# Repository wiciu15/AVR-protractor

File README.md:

# AVR-protractor
ATMega8 based protractor with SSD1306 OLED and LIS3DH accelerometer.

Schematic and PCB made in KiCAD. Firmware project created in Atmel Studio 7. Makefile available.

Known issue - ISP header is flipped, don't try to connect it to AVRISP with kanda ribbon cable, it's gonna make a short.

Firmware is working, but some extra features are still WIP (@TODO in main.c)

Display driver made by @tibounise (https://github.com/tibounise/SSD1306-AVR) slightly modified by me to save RAM for framebuffer.

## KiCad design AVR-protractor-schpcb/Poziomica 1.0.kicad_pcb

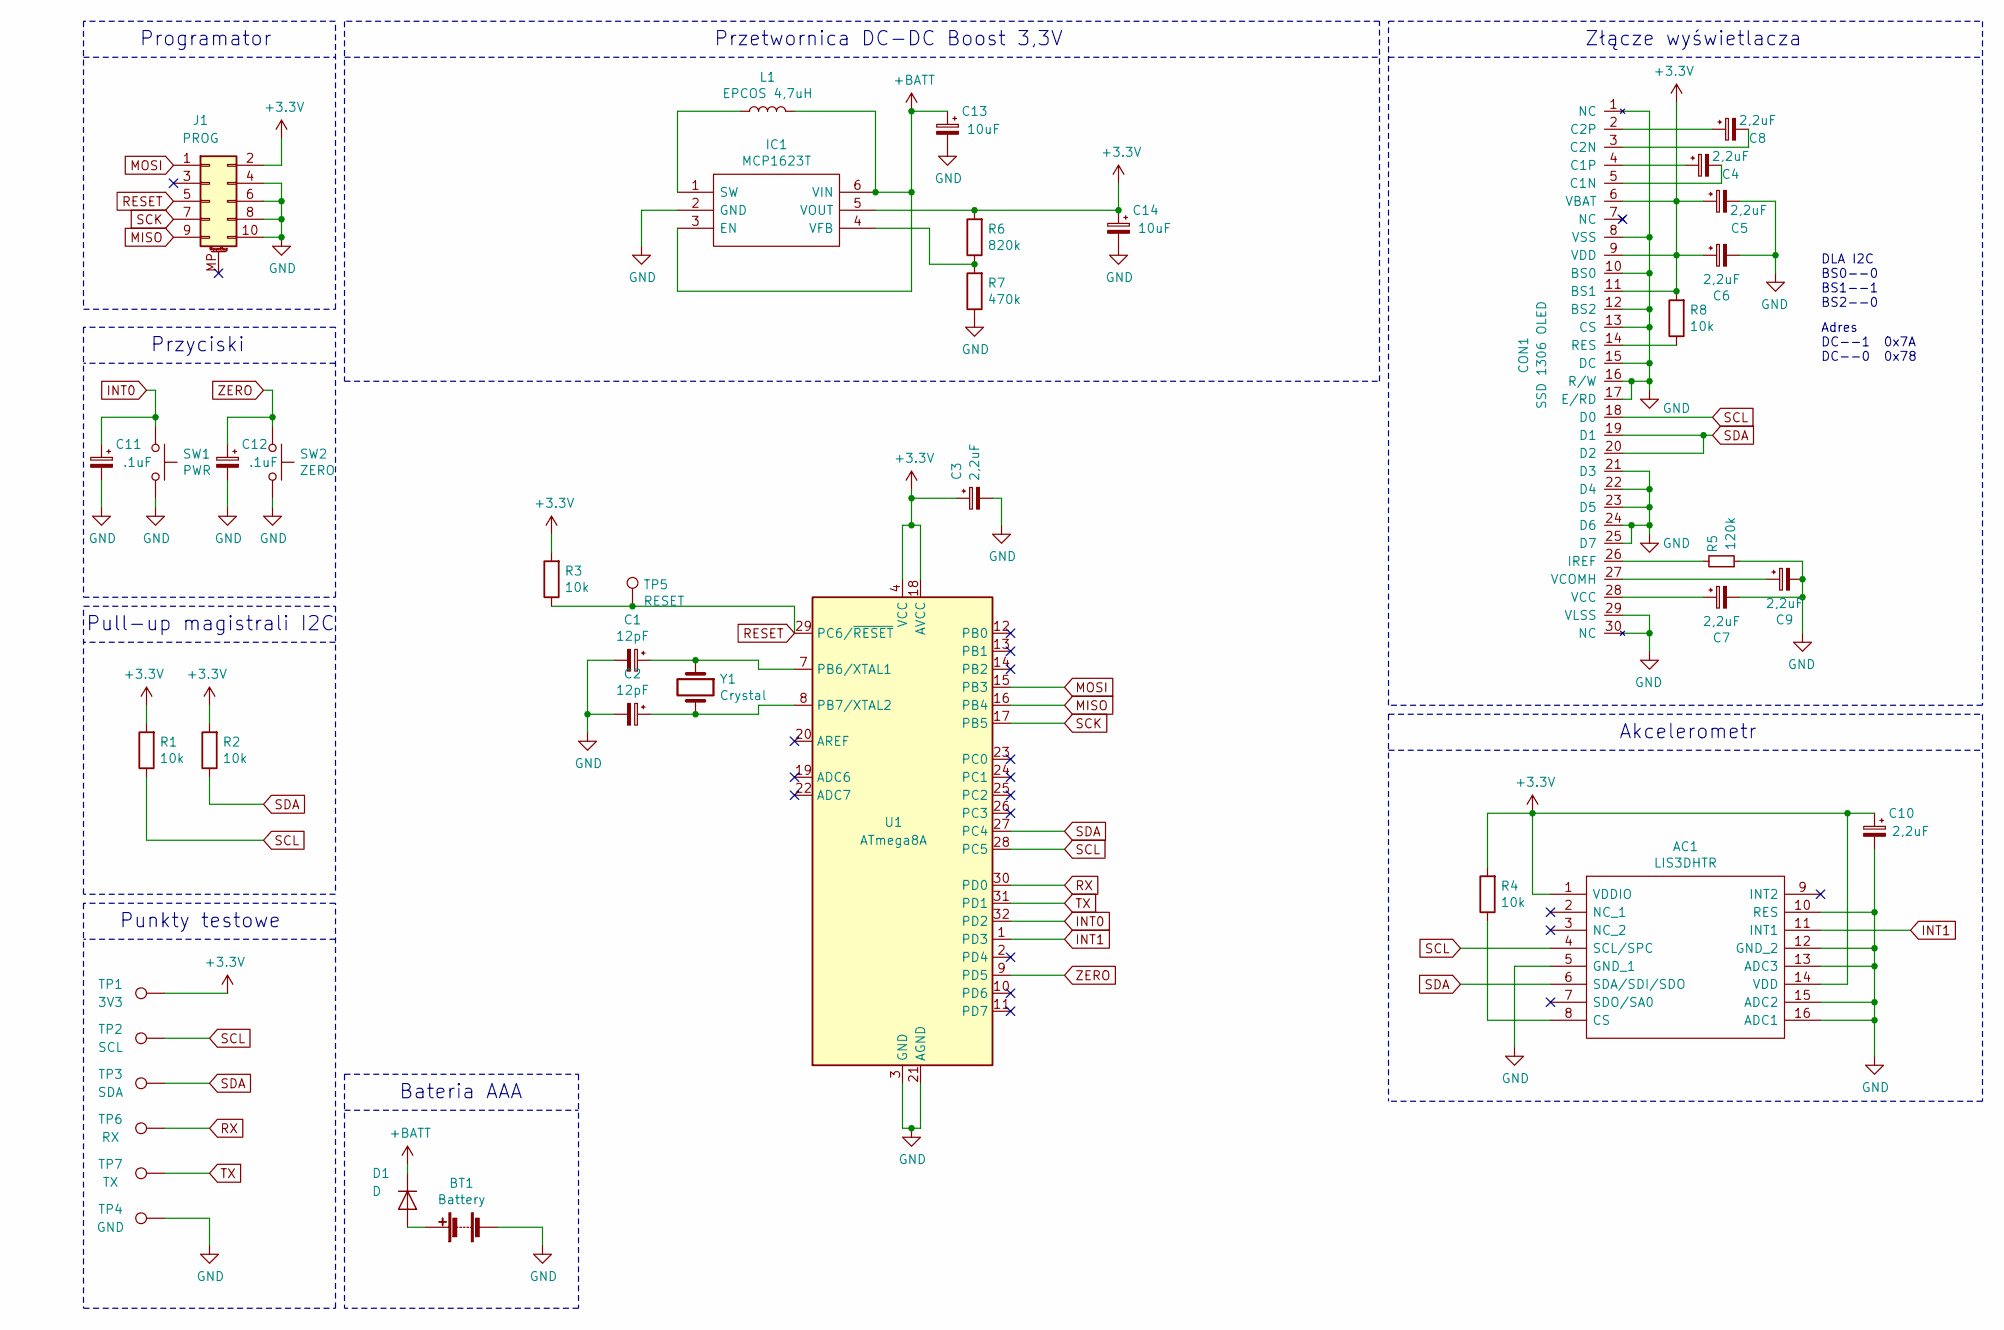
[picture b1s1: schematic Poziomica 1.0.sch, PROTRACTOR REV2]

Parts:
AC1: LIS3DHTR; LIS3DH_BigPad; Mouser Part Number 511-LIS3DHTR
BT1: Battery; 1021BatteryAAA
C1, C2: 12pF; C_0805_2012Metric_Pad1.15x1.40mm_HandSolder
C3, C4, C5, C6, C7, C8, C9, C10: 2,2uF; C_0805_2012Metric_Pad1.15x1.40mm_HandSolder
C11, C12: .1uF; C_0603_1608Metric_Pad1.05x0.95mm_HandSolder
C13, C14: 10uF; C_0805_2012Metric_Pad1.15x1.40mm_HandSolder
CON1: SSD 1306 OLED; SSD1306
D1: D; D_SOT-23_ANK
IC1: MCP1623T; SOT95P270X145-6N; Mouser Part Number 579-MCP1623T-I/CHY
J1: PROG
L1: EPCOS 4,7uH; IND-B82462G4
R1, R2, R3, R4, R8: 10k; R_0805_2012Metric_Pad1.15x1.40mm_HandSolder
R5: 120k; R_1206_3216Metric_Pad1.42x1.75mm_HandSolder
R6: 820k; R_0805_2012Metric_Pad1.15x1.40mm_HandSolder
R7: 470k; R_0805_2012Metric_Pad1.15x1.40mm_HandSolder
SW1: PWR; 7914J1000E
SW2: ZERO; 7914J1000E
TP1: 3V3; TestPoint_Pad_D2.0mm
TP2: SCL; TestPoint_Pad_D2.0mm
TP3: SDA; TestPoint_Pad_D2.0mm
TP4: GND; TestPoint_Pad_D2.0mm
TP5: RESET; TestPoint_Pad_D2.0mm
TP6: RX; TestPoint_Pad_D2.0mm
TP7: TX; TestPoint_Pad_D2.0mm
U1: ATmega8A; TQFP-32_7x7mm_P0.8mm
Y1: Crystal; Crystal_HC49-U_Vertical

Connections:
+3V3: AC1.1 (VDDIO), AC1.14 (VDD), C3.1, C5.1, C6.1, C10.1, C14.1, CON1.6 (VBAT), CON1.9 (VDD), CON1.11 (BS1), IC1.5 (VOUT), J1.2, R1.2, R2.2, R3.2, R4.2, R6.2, R8.2, TP1.1, U1.4 (VCC), U1.6 (VCC), U1.18 (AVCC)
+BATT: C13.1, D1.1 (K), IC1.3 (EN), IC1.6 (VIN), L1.2
GND: AC1.5 (GND_1), AC1.10 (RES), AC1.12 (GND_2), AC1.13 (ADC3), AC1.15 (ADC2), AC1.16 (ADC1), BT1.2 (-), C1.2, C2.2, C3.2, C5.2, C6.2, C7.2, C9.2, C10.2, C11.2, C12.2, C13.2, C14.2, CON1.1 (NC), CON1.8 (VSS), CON1.10 (BS0), CON1.12 (BS2), CON1.13 (CS), CON1.15 (DC), CON1.16 (R/W), CON1.17 (E/RD), CON1.21 (D3), CON1.22 (D4), CON1.23 (D5), CON1.24 (D6), CON1.25 (D7), CON1.29 (VLSS), CON1.30 (NC), IC1.2 (GND), J1.4, J1.6, J1.8, J1.10, R5.1, R7.1, SW1.2, SW2.2, TP4.1, U1.3 (GND), U1.5 (GND), U1.21 (AGND)
INT0: C11.1, SW1.1, U1.32 (PD2)
INT1: AC1.11 (INT1), U1.1 (PD3)
MISO: J1.9, U1.16 (PB4)
MOSI: J1.1, U1.15 (PB3)
unnamed: AC1.8 (CS), R4.1
unnamed: BT1.1 (+), D1.2 (A)
unnamed: C1.1, U1.7 (PB6/XTAL1), Y1.1
unnamed: C2.1, U1.8 (PB7/XTAL2), Y1.2
unnamed: C4.1, CON1.4 (C1P)
unnamed: C4.2, CON1.5 (C1N)
unnamed: C7.1, CON1.28 (VCC)
unnamed: C8.1, CON1.2 (C2P)
unnamed: C8.2, CON1.3 (C2N)
unnamed: C9.1, CON1.27 (VCOMH)
unnamed: CON1.14 (RES), R8.1
unnamed: CON1.26 (IREF), R5.2
unnamed: IC1.1 (SW), L1.1
unnamed: IC1.4 (VFB), R6.1, R7.2
RESET: J1.5, R3.1, TP5.1, U1.29 (PC6/~RESET)
RX: TP6.1, U1.30 (PD0)
SCK: J1.7, U1.17 (PB5)
SCL: AC1.4 (SCL/SPC), CON1.18 (D0), R1.1, TP2.1, U1.28 (PC5)
SDA: AC1.6 (SDA/SDI/SDO), CON1.19 (D1), CON1.20 (D2), R2.1, TP3.1, U1.27 (PC4)
TX: TP7.1, U1.31 (PD1)
ZERO: C12.1, SW2.1, U1.9 (PD5)

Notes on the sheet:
DLA I2C BS0--0 BS1--1 BS2--0
Złącze wyświetlacza
Akcelerometr
Punkty testowe
Pull-up magistrali I2C
Przyciski
Programator
Bateria AAA
Przetwornica DC-DC Boost 3,3V
Adres DC--1 0x7A DC--0 0x78

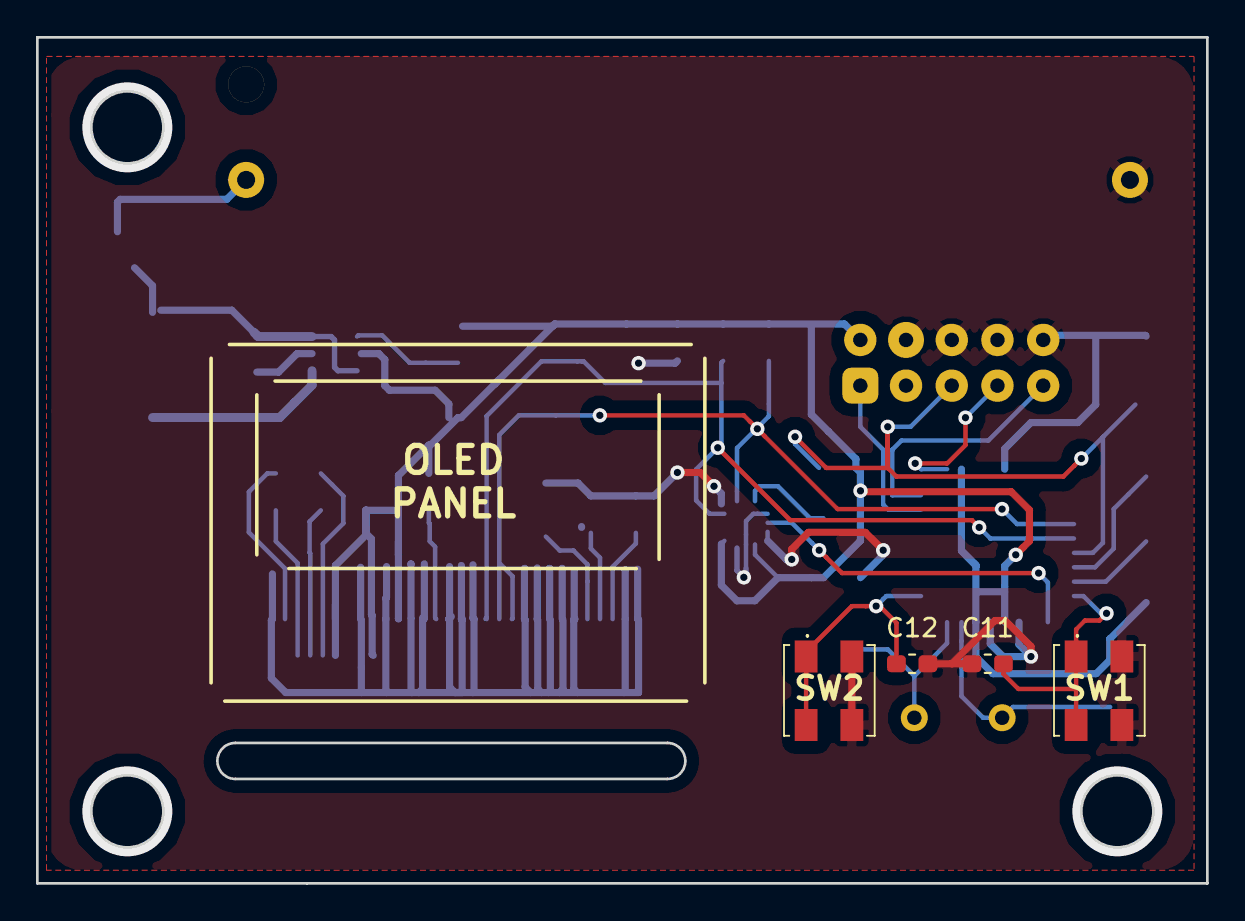
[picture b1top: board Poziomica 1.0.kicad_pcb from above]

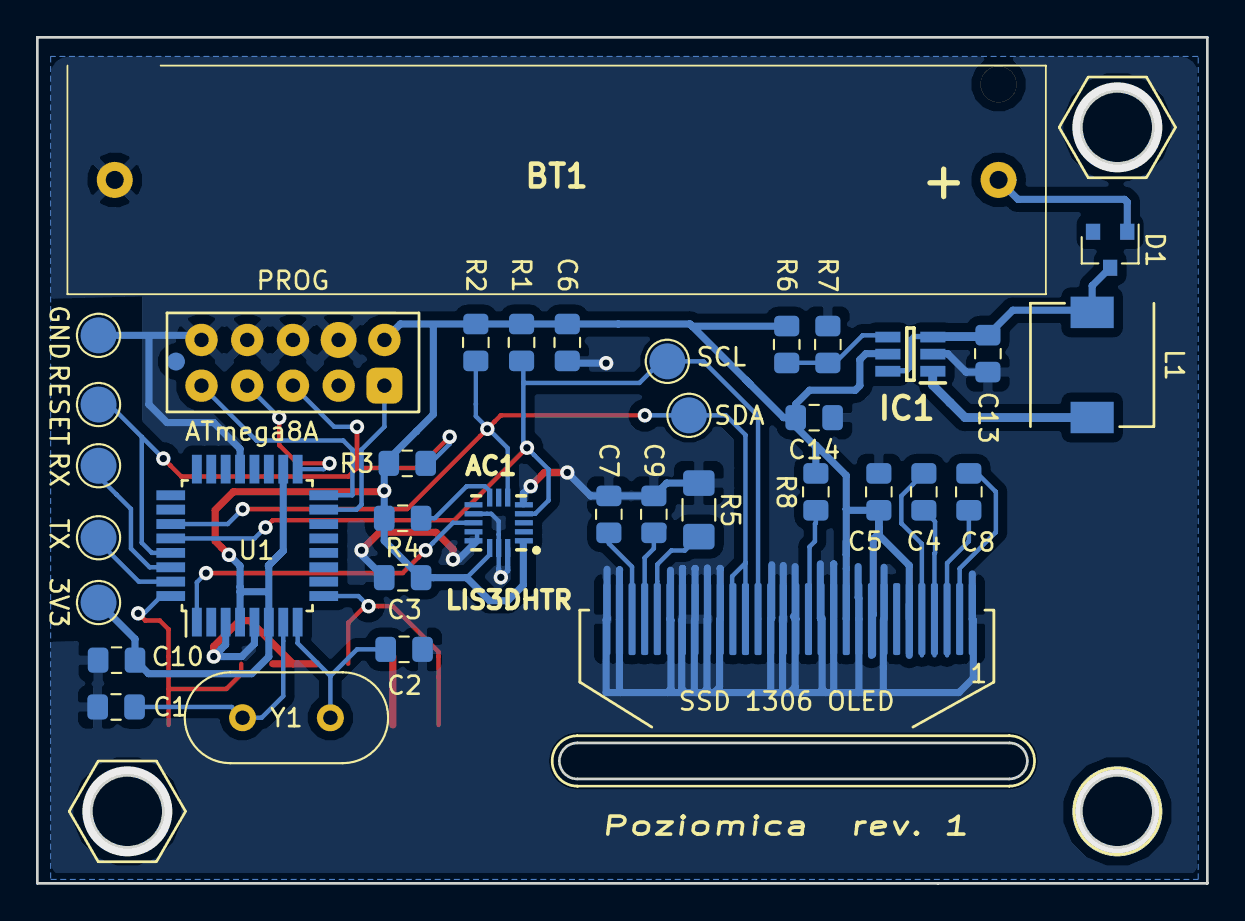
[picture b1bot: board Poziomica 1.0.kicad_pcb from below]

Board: 2 copper layers, 65.0 x 47.0 mm, 40 parts (36 on the bottom side), 28 nets.

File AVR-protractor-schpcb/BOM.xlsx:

Source: | C:\Users\wiki1\Documents\kicad\Poziomica 1.0\Poziomica 1.0.sch
Date: | 43485.064756944441
Tool: | Eeschema (5.0.2)-1
Generator: | C:\Program Files\KiCad\bin\scripting\plugins/bom_csv_grouped_by_value.py
Component Count: | 31
Collated Components:
Item | Qty | Reference(s) | Value | LibPart | Footprint | zamowiony | kupiony | doszedl | Cena/szt | Cena/PCB
1 | 1 | AC1 | LIS3DHTR | SamacSys_Parts:LIS3DHTR | SSD1306:LIS3DH | kamami | 1 | 1 | 4.9000000000000004 | 4.9000000000000004
2 | 1 | BT1 | Battery | Device:Battery | SSD1306:1021BatteryAAA | allegro-sm | 1 |  | 3 | 3
3 | 2 | C1, C2 | 12pF | Device:CP_Small | Capacitor_SMD:C_0805_2012Metric_Pad1.15x1.40mm_HandSolder | allegro-sm | 1 |  | 0.05 | 0.1
4 | 8 | C3, C4, C5, C6, C7, C8, C9, C10 | 2,2uF | Device:CP_Small | Capacitor_SMD:C_0805_2012Metric_Pad1.15x1.40mm_HandSolder | allegro-sm | 1 |  | 0.05 | 0.4
5 | 2 | C11, C12 | .1uF | Device:CP_Small | Capacitor_SMD:C_0603_1608Metric_Pad1.05x0.95mm_HandSolder | allegro-sm | 1 |  | 0.05 | 0.1
6 | 2 | C13, C14 | 10uF | Device:CP_Small | Capacitor_SMD:C_0805_2012Metric_Pad1.15x1.40mm_HandSolder | allegro-sm | 1 |  | 0.05 | 0.1
7 | 1 | CON1 | SSD 1306 OLED | SSD1306:OLED | SSD1306:SSD1306 | allegro artronic | 1 | 1 | 19.399999999999999 | 19.399999999999999
8 | 1 | IC1 | MCP1623T-I_CHY | SamacSys_Parts:MCP1623T-I_CHY | SamacSys_Parts:SOT95P270X145-6N | tme | 1 | 1 | 2.16 | 2.16
9 | 1 | J1 | Conn_02x05_Odd_Even | Connector_Generic_MountingPin:Conn_02x05_Odd_Even_MountingPin | SSD1306:PROG | w domu | 1 | 1 | 0.3 | 0.3
10 | 1 | L1 | DLG-0403-4R7 | Device:L | SSD1306:IND-B82462G4 | allegro-sm | 1 |  | 2.46 | 2.46
11 | 4 | R1, R2, R3, R4 | 10k | Device:R | Resistor_SMD:R_0805_2012Metric_Pad1.15x1.40mm_HandSolder | allegro-sm | 1 |  | 0.05 | 0.2
12 | 1 | R5 | 120k | Device:R_Small | Resistor_SMD:R_1206_3216Metric_Pad1.42x1.75mm_HandSolder | allegro-sm | 1 |  | 0.05 | 0.05
13 | 1 | R6 | 820k | Device:R | Resistor_SMD:R_0805_2012Metric_Pad1.15x1.40mm_HandSolder | allegro-sm | 1 |  | 0.05 | 0.05
14 | 1 | R7 | 470k | Device:R | Resistor_SMD:R_0805_2012Metric_Pad1.15x1.40mm_HandSolder | allegro-sm | 1 |  | 0.05 | 0.05
15 | 1 | SW1 | PWR | Switch:SW_Push | SamacSys_Parts:7914J1000E | allegro-sm | 1 |  | 1.23 | 1.23
16 | 1 | SW2 | ZERO | Switch:SW_Push | SamacSys_Parts:7914J1000E | allegro-sm | 1 |  | 1.23 | 1.23
17 | 1 | U1 | ATmega8A-AU | MCU_Microchip_ATmega:ATmega8A-AU | Package_QFP:TQFP-32_7x7mm_P0.8mm | allegro-artronic | 1 | 1 | 4.5 | 4.5
18 | 1 | Y1 | Crystal | Device:Crystal | SSD1306:Crystal_HC49-U_Vertical | allegro-artronic | 1 | 1 | 0.5 | 0.5
 |  |  |  |  |  |  |  |  |  | 40.72999999999999

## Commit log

2020-02-24 debug/make files deleted from repo
2020-02-24 added 1-axis bubble mode when device is on the side
2020-02-27 added defines for accelerometer registers
